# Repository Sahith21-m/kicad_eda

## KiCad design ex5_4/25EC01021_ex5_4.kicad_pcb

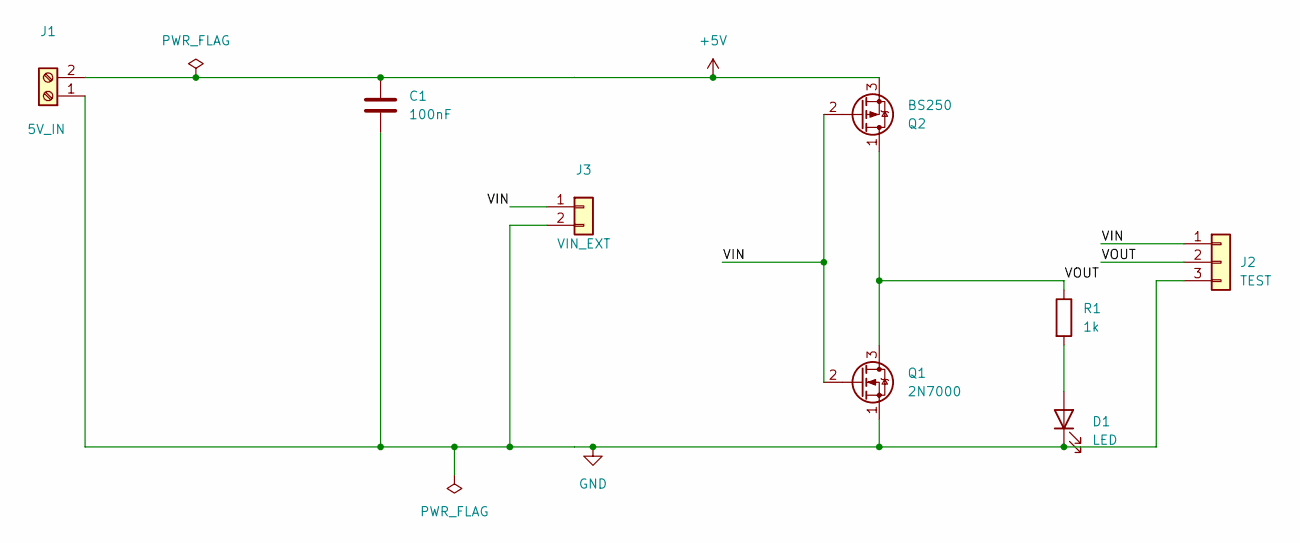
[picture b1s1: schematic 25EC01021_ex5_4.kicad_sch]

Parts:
C1: 100nF; C_Disc_D5.0mm_W2.5mm_P5.00mm
D1: LED; LED_D3.0mm
J1: 5V_IN; TerminalBlock_Phoenix_MKDS-1,5-2-5.08_1x02_P5.08mm_Horizont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
J2: TEST; PinHeader_1x03_P2.54mm_Vertical
J3: VIN_EXT; PinHeader_1x02_P2.54mm_Vertical
Q1: 2N7000; TO-92_Inline
Q2: BS250; TO-92_Inline
R1: 1k; R_Axial_DIN0207_L6.3mm_D2.5mm_P10.16mm_Horizontal

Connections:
+5V: C1.1, J1.2, Q2.3 (S)
/VIN: J2.1, J3.1, Q1.2 (G), Q2.2 (G)
/VOUT: J2.2, Q1.3 (D), Q2.1 (D), R1.1
GND: C1.2, D1.1 (K), J1.1, J2.3, J3.2, Q1.1 (S)
unnamed: D1.2 (A), R1.2

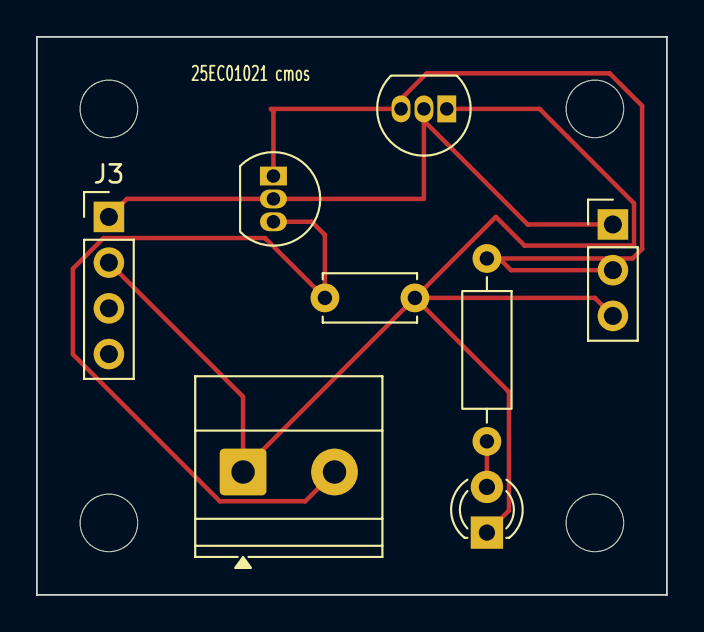
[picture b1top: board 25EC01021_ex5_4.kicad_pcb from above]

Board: 2 copper layers, 35.0 x 31.0 mm, 8 parts (0 on the bottom side), 5 nets.

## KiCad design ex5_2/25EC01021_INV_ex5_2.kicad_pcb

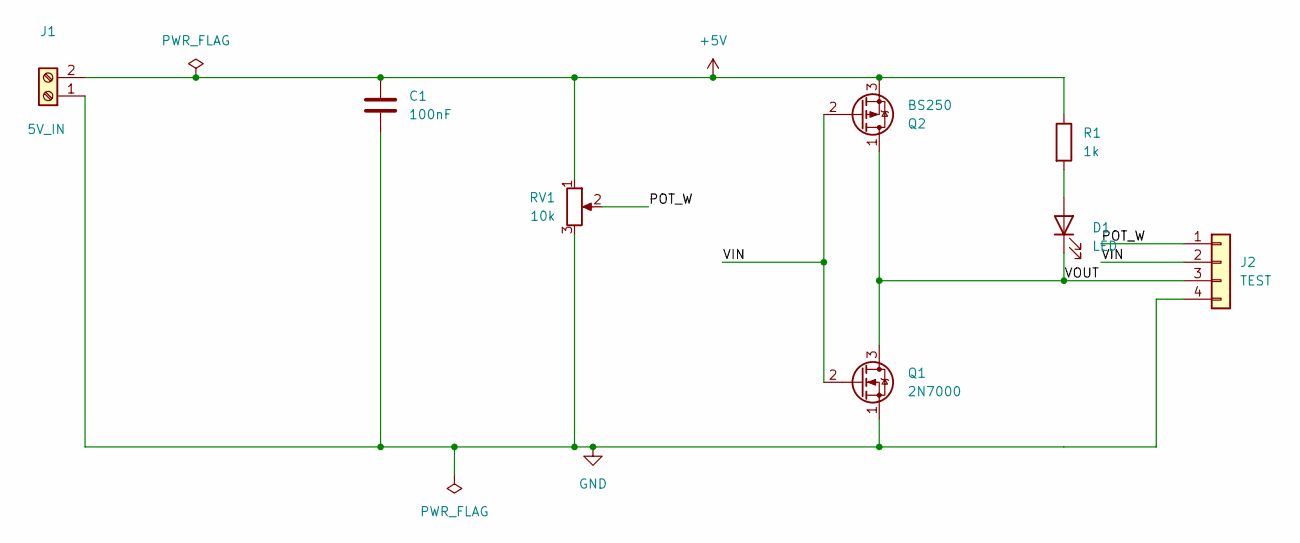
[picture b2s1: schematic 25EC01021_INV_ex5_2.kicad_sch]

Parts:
C1: 100nF; C_Disc_D5.0mm_W2.5mm_P5.00mm
D1: LED; LED_D3.0mm
J1: 5V_IN; TerminalBlock_Phoenix_MKDS-1,5-2-5.08_1x02_P5.08mm_Horizont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
J2: TEST; PinHeader_1x04_P2.54mm_Vertical
Q1: 2N7000; TO-92_Inline
Q2: BS250; TO-92_Inline
R1: 1k; R_Axial_DIN0207_L6.3mm_D2.5mm_P10.16mm_Horizontal
RV1: 10k; Potentiometer_Bourns_3386P_Vertical

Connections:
+5V: C1.1, J1.2, Q2.3 (S), R1.1, RV1.1
/POT_W: J2.1, RV1.2
/VIN: J2.2, Q1.2 (G), Q2.2 (G)
/VOUT: D1.1 (K), J2.3, Q1.3 (D), Q2.1 (D)
GND: C1.2, J1.1, J2.4, Q1.1 (S), RV1.3
unnamed: D1.2 (A), R1.2

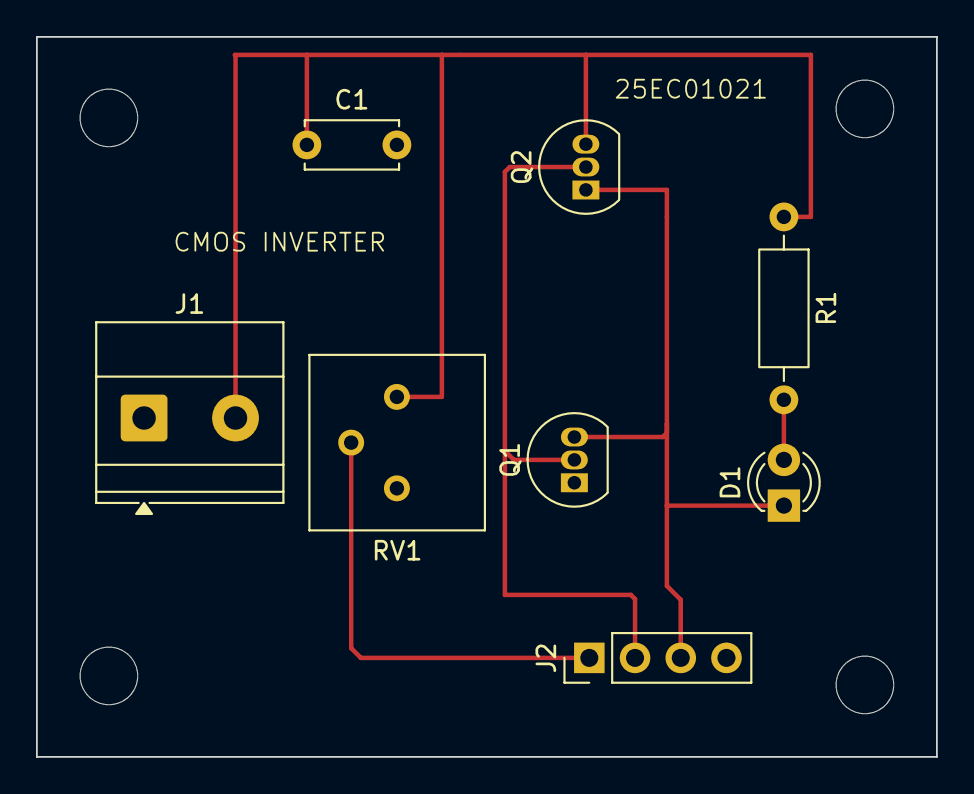
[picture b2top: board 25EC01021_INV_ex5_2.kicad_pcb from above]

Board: 2 copper layers, 50.0 x 40.0 mm, 8 parts (0 on the bottom side), 6 nets.
